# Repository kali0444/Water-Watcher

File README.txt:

*** WATER WATCHER (aka Water Pump Controller) ***

Hello all genius minds.
This is my first design as a Beginner PCB Designer,

- Working- Whenever needed, i manually switch ON the wall socket switch to run motor and motor will automatically stop and indicator led starts blinking and buzzer making sound to alert me when the water tank is full, then i will manually switch OFF the wall socket switch.

- I have used NE556 Timer IC to build it.
- I have used connector -J1 for my system powering (~5VDC), 
			-J2 (2 pins will be at the top portion inside the tank and get short when water reaches the maximum 				height),
			-J3 (a switch)for bypass my system in case of issue, 
			-J4 for controlling my 1HP water pump (Live wire).

- I appreciate if you guide me to make it better and efficient.

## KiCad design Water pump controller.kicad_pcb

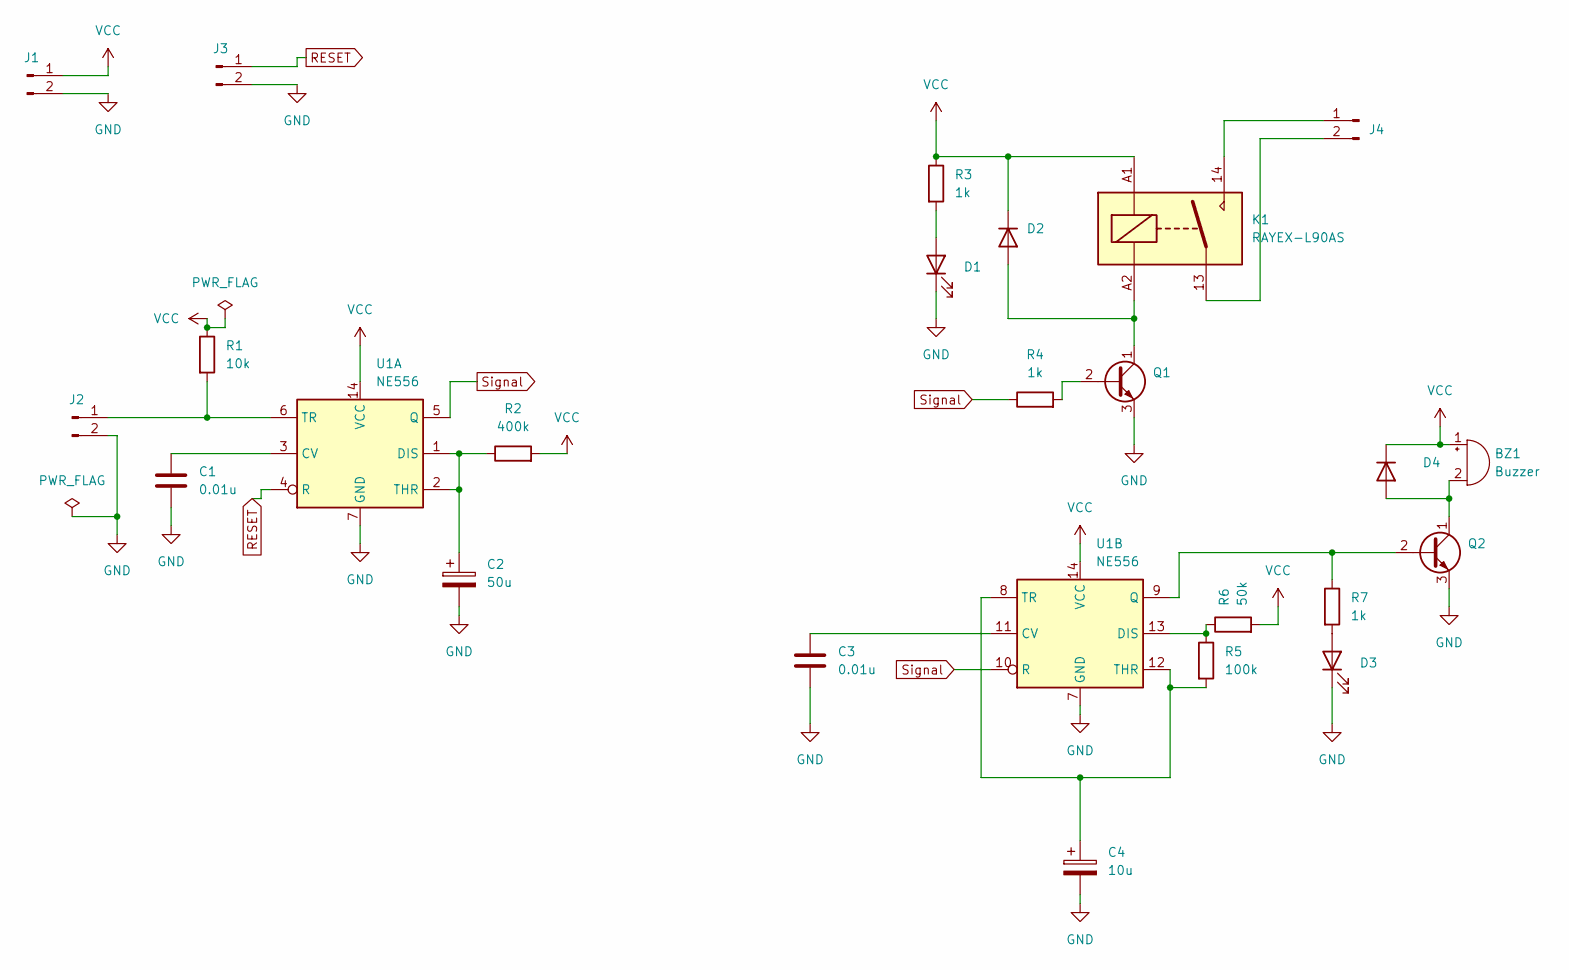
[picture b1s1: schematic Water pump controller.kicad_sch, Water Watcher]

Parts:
BZ1: Buzzer; Buzzer_12x9.5RM7.6
C1, C3: 0.01u; C_Disc_D3.8mm_W2.6mm_P2.50mm
C2: 50u; CP_Radial_D5.0mm_P2.00mm
C4: 10u; CP_Radial_D4.0mm_P1.50mm
D1, D3: LED; LED_D5.0mm
D2, D4: 1N4001; D_DO-41_SOD81_P10.16mm_Horizontal
J1, J2, J3, J4: Conn_01x02_Pin; TerminalBlock_bornier-2_P5.08mm
K1: RAYEX-L90AS; Relay_SPST_RAYEX-L90AS
Q1, Q2: BC549; TO-92_Inline
R1: 10k; R_Axial_DIN0204_L3.6mm_D1.6mm_P5.08mm_Horizontal
R2: 400k; R_Axial_DIN0204_L3.6mm_D1.6mm_P5.08mm_Horizontal
R3, R4, R7: 1k; R_Axial_DIN0204_L3.6mm_D1.6mm_P5.08mm_Horizontal
R5: 100k; R_Axial_DIN0204_L3.6mm_D1.6mm_P5.08mm_Horizontal
R6: 50k; R_Axial_DIN0204_L3.6mm_D1.6mm_P5.08mm_Horizontal
U1: NE556; CERDIP-14_W7.62mm_SideBrazed

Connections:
GND: C1.2, C2.2, C3.2, C4.2, D1.1 (K), D3.1 (K), J1.2, J2.2, J3.2, Q1.3 (E), Q2.3 (E), U1.7 (GND)
unnamed: BZ1.2 (-), D4.2 (A), Q2.1 (C)
unnamed: D1.2 (A), R3.2
unnamed: D2.2 (A), K1.A2, Q1.1 (C)
unnamed: D3.2 (A), R7.2
unnamed: J2.1, R1.2, U1.6 (TR)
unnamed: J4.1, K1.14
unnamed: J4.2, K1.13
unnamed: Q1.2 (B), R4.2
unnamed: Q2.2 (B), R7.1, U1.9 (Q)
unnamed: C1.1, U1.3 (CV)
unnamed: C2.1, R2.1, U1.1 (DIS), U1.2 (THR)
unnamed: C3.1, U1.11 (CV)
unnamed: R5.1, R6.1, U1.13 (DIS)
unnamed: C4.1, R5.2, U1.8 (TR), U1.12 (THR)
RESET: J3.1, U1.4 (R)
Signal: R4.1, U1.5 (Q), U1.10 (R)
VCC: BZ1.1 (+), D2.1 (K), D4.1 (K), J1.1, K1.A1, R1.1, R2.2, R3.1, R6.2, U1.14 (VCC)

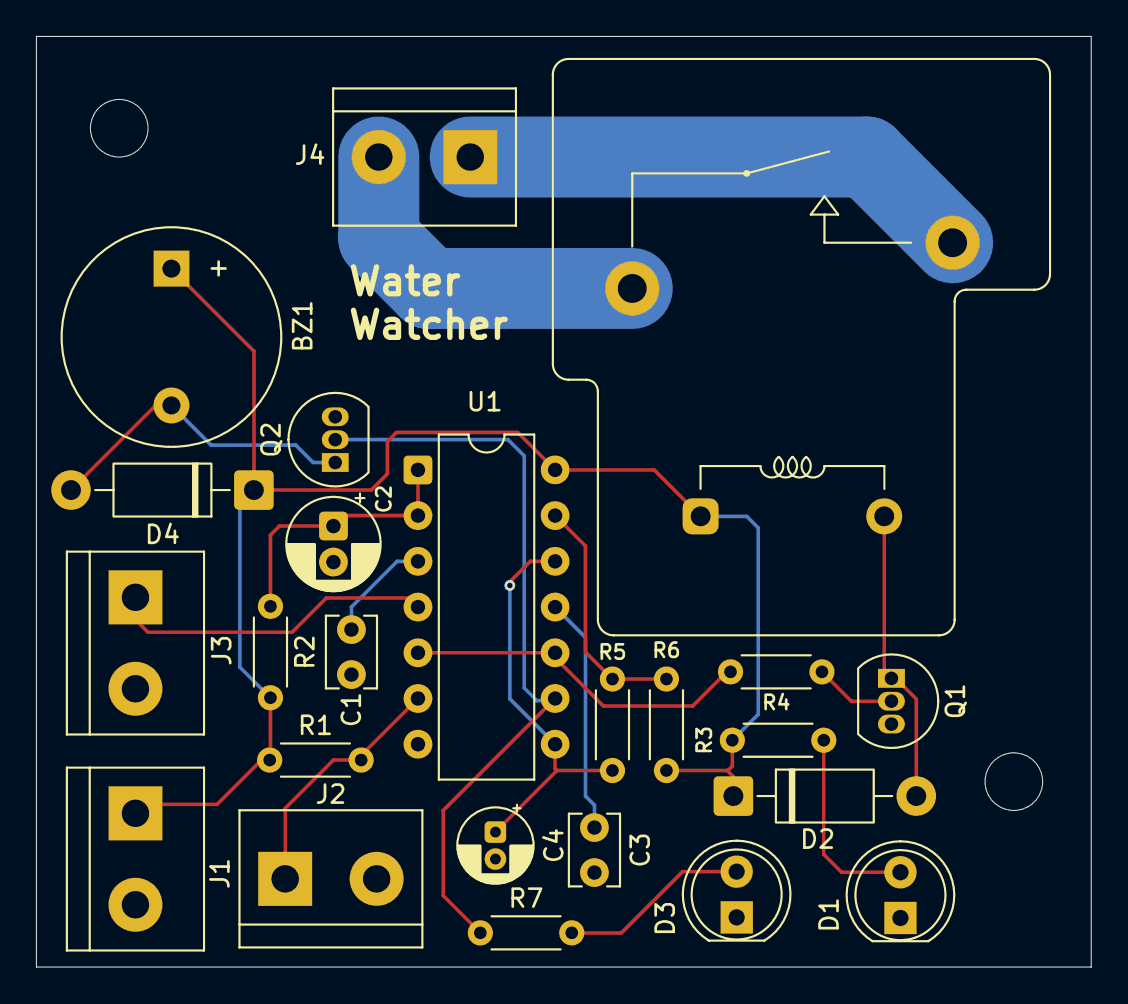
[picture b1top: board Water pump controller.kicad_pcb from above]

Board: 2 copper layers, 58.6 x 51.7 mm, 24 parts (0 on the bottom side), 18 nets.

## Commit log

2025-09-14 Initial commit of KiCad project
    Add all essential files for a new project, including the schematic, board layout, README, and .gitignore.
2025-09-14 Add CC-BY-SA 4.0 license file
2025-09-14 Initial commit of KiCad project
